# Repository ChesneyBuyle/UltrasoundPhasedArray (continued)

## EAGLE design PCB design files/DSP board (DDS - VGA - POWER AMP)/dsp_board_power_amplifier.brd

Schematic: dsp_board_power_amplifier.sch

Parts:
C1, C19, C28, C37, C55, C64, C73, C91, C100, C109, C127, C136, C154, C172, C190, C208: 1u@6.3V; C0805
C2, C20, C29, C38, C56, C65, C74, C92, C101, C110, C128, C137, C155, C173, C191, C209: 1u6.3V; C0805
C3, C21, C30, C39, C57, C66, C75, C93, C102, C111, C129, C138, C156, C174, C192, C210: 1u; C0603
C4, C11, C12, C22, C31, C40, C47, C48, C58, C67, C76, C84, C85, C94, C103, C112, C121, C122, C130, C139, C157, C175, C193, C211: 10u; C0805
C5, C26, C35, C44, C62, C71, C80, C98, C107, C116, C134, C143, C161, C179, C197, C215: 1u@10V; C0603
C6, C27, C36, C45, C63, C72, C81, C99, C108, C117, C135, C144, C162, C180, C198, C216: 4.7u@25V; C0603
C7, C8, C23, C24, C32, C33, C41, C42, C59, C60, C68, C69, C77, C78, C95, C96, C104, C105, C113, C114, C131, C132, C140, C141, C158, C159, C176, C177, C194, C195, C212, C213: 1u@35V; C0603
C9, C25, C34, C43, C61, C70, C79, C97, C106, C115, C133, C142, C160, C178, C196, C214: 1u@25V; C0603
C10, C13, C14: 100 µF; WCAP-ASLU_6.3X7.7(DXL)
C15, C49, C86, C123: 100n; C0603
C16, C17, C50, C51, C87, C88, C124, C125: 22u; C1206
INPUT: 1935161; PHOENIX_1935161
JP1, JP2, JP5, JP6, JP7, JP8, JP9, JP10, JP13, JP14, JP15, JP16, JP17, JP18, JP21, JP22, JP23, JP24, JP25, JP26, JP29, JP30, JP31, JP32, JP35, JP36, JP39, JP40, JP43, JP44, JP47, JP48: PINHD-1X2; 1X02
L1, L5, L7, L9, L13, L15, L17, L21, L23, L25, L29, L31, L35, L39, L43, L47: BRL3225T4R7M 4.7u; INDC3225X170N
L2, L11, L19, L27: 3.3uH; WE-PD_7345P
L3, L6, L8, L10, L14, L16, L18, L22, L24, L26, L30, L32, L36, L40, L44, L48: FDSD0420-H-100M=P3; IND_FDSD0420-H-100M=P3
LSP1, LSP2, LSP3, LSP4: LSP10
R1, R2, R4, R12, R13, R14, R19, R20, R25, R26, R34, R37, R38, R43, R44, R49, R50, R56, R61, R62, R67, R68, R73, R74, R85, R86, R91, R92, R103, R104, R115, R116, R127, R128, R139, R140: 10k; R0603
R3, R11, R33, R55: 33k; R0603
R5, R6, R15, R16, R21, R22, R27, R28, R39, R40, R45, R46, R51, R52, R63, R64, R69, R70, R75, R76, R87, R88, R93, R94, R105, R106, R117, R118, R129, R130, R141, R142: 10; R0603
R7, R17, R23, R29, R41, R47, R53, R65, R71, R77, R89, R95, R107, R119, R131, R143: 18k; R0603
R8, R18, R24, R30, R42, R48, R54, R66, R72, R78, R90, R96, R108, R120, R132, R144: 1k; R0603
SJ1, SJ2, SJ5, SJ7, SJ9, SJ11, SJ13, SJ15, SJ17, SJ19, SJ21, SJ23, SJ25, SJ27, SJ29, SJ31, SJ35, SJ39, SJ43, SJ47: SJ
SJ3, SJ6, SJ8, SJ10, SJ14, SJ16, SJ18, SJ22, SJ24, SJ26, SJ30, SJ32, SJ36, SJ40, SJ44, SJ48: SJ2W; SJ_2
U1, U6, U8, U10, U14, U16, U18, U22, U24, U26, U30, U32, U36, U40, U44, U48: TLV61046ADBVR; SOT95P280X145-6N
U2, U5, U7, U9, U13, U15, U17, U21, U23, U25, U29, U31, U35, U39, U43, U47: LM48580; BGA12N40P3X4_119X159X62N
U$1, U$10, U$17, U$21: TPS562209; SOT95P280X110-6N
U$2, U$3, U$4, U$5, U$7, U$8, U$9, U$11, U$12, U$13, U$15, U$16, U$18, U$20, U$22, U$24: NSR0520V2T1G; SOD523

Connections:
15V_1: C6.1, R1.2, R7.2, U1.5 (VOUT)
15V_2: C27.1, R13.2, R17.2, U6.5 (VOUT)
15V_3: C45.1, R25.2, R29.2, U10.5 (VOUT)
15V_4: C63.1, R37.2, R41.2, U14.5 (VOUT)
15V_5: C81.1, R49.2, R53.2, U18.5 (VOUT)
15V_6: C99.1, R61.2, R65.2, U22.5 (VOUT)
15V_7: C117.1, R73.2, R77.2, U26.5 (VOUT)
15V_8: C135.1, R85.2, R89.2, U30.5 (VOUT)
15V_9: C36.1, R19.2, R23.2, U8.5 (VOUT)
15V_10: C72.1, R43.2, R47.2, U16.5 (VOUT)
15V_11: C108.1, R67.2, R71.2, U24.5 (VOUT)
15V_12: C144.1, R91.2, R95.2, U32.5 (VOUT)
15V_13: C162.1, R103.2, R107.2, U36.5 (VOUT)
15V_14: C180.1, R115.2, R119.2, U40.5 (VOUT)
15V_15: C198.1, R127.2, R131.2, U44.5 (VOUT)
15V_16: C216.1, R139.2, R143.2, U48.5 (VOUT)
+3V3_A: C3.1, C4.1, C5.1, C16.1, C17.1, C21.1, C22.1, C26.1, C39.1, C40.1, C44.1, C57.1, C58.1, C62.1, L1.1, L2.2, L3.1, L5.1, L6.1, L9.1, L10.1, L13.1, L14.1, R3.2, SJ1.2, SJ3.1, SJ6.1, SJ10.1, SJ14.1, U1.4 (EN), U1.6 (VIN), U2.C2 (~SHDN), U2.C3 (VDD), U5.C2 (~SHDN), U5.C3 (VDD), U6.4 (EN), U6.6 (VIN), U9.C2 (~SHDN), U9.C3 (VDD), U10.4 (EN), U10.6 (VIN), U13.C2 (~SHDN), U13.C3 (VDD), U14.4 (EN), U14.6 (VIN)
+3V3_B: C50.1, C51.1, C75.1, C76.1, C80.1, C93.1, C94.1, C98.1, C111.1, C112.1, C116.1, C129.1, C130.1, C134.1, L11.2, L17.1, L18.1, L21.1, L22.1, L25.1, L26.1, L29.1, L30.1, R11.2, SJ11.2, SJ18.1, SJ22.1, SJ26.1, SJ30.1, U17.C2 (~SHDN), U17.C3 (VDD), U18.4 (EN), U18.6 (VIN), U21.C2 (~SHDN), U21.C3 (VDD), U22.4 (EN), U22.6 (VIN), U25.C2 (~SHDN), U25.C3 (VDD), U26.4 (EN), U26.6 (VIN), U29.C2 (~SHDN), U29.C3 (VDD), U30.4 (EN), U30.6 (VIN)
+3V3_C: C30.1, C31.1, C35.1, C66.1, C67.1, C71.1, C87.1, C88.1, C102.1, C103.1, C107.1, C138.1, C139.1, C143.1, L7.1, L8.1, L15.1, L16.1, L19.2, L23.1, L24.1, L31.1, L32.1, R33.2, SJ8.1, SJ16.1, SJ19.2, SJ24.1, SJ32.1, U7.C2 (~SHDN), U7.C3 (VDD), U8.4 (EN), U8.6 (VIN), U15.C2 (~SHDN), U15.C3 (VDD), U16.4 (EN), U16.6 (VIN), U23.C2 (~SHDN), U23.C3 (VDD), U24.4 (EN), U24.6 (VIN), U31.C2 (~SHDN), U31.C3 (VDD), U32.4 (EN), U32.6 (VIN)
+3V3_D: C124.1, C125.1, C156.1, C157.1, C161.1, C174.1, C175.1, C179.1, C192.1, C193.1, C197.1, C210.1, C211.1, C215.1, L27.2, L35.1, L36.1, L39.1, L40.1, L43.1, L44.1, L47.1, L48.1, R55.2, SJ27.2, SJ36.1, SJ40.1, SJ44.1, SJ48.1, U35.C2 (~SHDN), U35.C3 (VDD), U36.4 (EN), U36.6 (VIN), U39.C2 (~SHDN), U39.C3 (VDD), U40.4 (EN), U40.6 (VIN), U43.C2 (~SHDN), U43.C3 (VDD), U44.4 (EN), U44.6 (VIN), U47.C2 (~SHDN), U47.C3 (VDD), U48.4 (EN), U48.6 (VIN)
GND: C3.2, C4.2, C5.2, C6.2, C9.1, C10.2 (-), C11.2, C12.2, C13.2 (-), C14.2 (-), C16.2, C17.2, C21.2, C22.2, C25.1, C26.2, C27.2, C30.2, C31.2, C34.1, C35.2, C36.2, C39.2, C40.2, C43.1, C44.2, C45.2, C47.2, C48.2, C50.2, C51.2, C57.2, C58.2, C61.1, C62.2, C63.2, C66.2, C67.2, C70.1, C71.2, C72.2, C75.2, C76.2, C79.1, C80.2, C81.2, C84.2, C85.2, C87.2, C88.2, C93.2, C94.2, C97.1, C98.2, C99.2, C102.2, C103.2, C106.1, C107.2, C108.2, C111.2, C112.2, C115.1, C116.2, C117.2, C121.2, C122.2, C124.2, C125.2, C129.2, C130.2, C133.1, C134.2, C135.2, C138.2, C139.2, C142.1, C143.2, C144.2, C156.2, C157.2, C160.1, C161.2, C162.2, C174.2, C175.2, C178.1, C179.2, C180.2, C192.2, C193.2, C196.1, C197.2, C198.2, C210.2, C211.2, C214.1, C215.2, C216.2, INPUT.2, LSP2.MP, LSP4.MP, R2.1, R4.1, R8.1, R12.1, R14.1, R18.1, R20.1, R24.1, R26.1, R30.1, R34.1, R38.1, R42.1, R44.1, R48.1, R50.1, R54.1, R56.1, R62.1, R66.1, R68.1, R72.1, R74.1, R78.1, R86.1, R90.1, R92.1, R96.1, R104.1, R108.1, R116.1, R120.1, R128.1, R132.1, R140.1, R144.1, SJ2.1, SJ3.3, SJ5.1, SJ6.3, SJ7.1, SJ8.3, SJ9.1, SJ10.3, SJ13.1, SJ14.3, SJ15.1, SJ16.3, SJ17.1, SJ18.3, SJ21.1, SJ22.3, SJ23.1, SJ24.3, SJ25.1, SJ26.3, SJ29.1, SJ30.3, SJ31.1, SJ32.3, SJ35.1, SJ36.3, SJ39.1, SJ40.3, SJ43.1, SJ44.3, SJ47.1, SJ48.3, U1.2 (GND), U2.A2 (SGND), U2.D3 (PGND), U5.A2 (SGND), U5.D3 (PGND), U6.2 (GND), U7.A2 (SGND), U7.D3 (PGND), U8.2 (GND), U9.A2 (SGND), U9.D3 (PGND), U10.2 (GND), U13.A2 (SGND), U13.D3 (PGND), U14.2 (GND), U15.A2 (SGND), U15.D3 (PGND), U16.2 (GND), U17.A2 (SGND), U17.D3 (PGND), U18.2 (GND), U21.A2 (SGND), U21.D3 (PGND), U22.2 (GND), U23.A2 (SGND), U23.D3 (PGND), U24.2 (GND), U25.A2 (SGND), U25.D3 (PGND), U26.2 (GND), U29.A2 (SGND), U29.D3 (PGND), U30.2 (GND), U31.A2 (SGND), U31.D3 (PGND), U32.2 (GND), U35.A2 (SGND), U35.D3 (PGND), U36.2 (GND), U39.A2 (SGND), U39.D3 (PGND), U40.2 (GND), U43.A2 (SGND), U43.D3 (PGND), U44.2 (GND), U47.A2 (SGND), U47.D3 (PGND), U48.2 (GND), U$1.1 (GND), U$10.1 (GND), U$17.1 (GND), U$21.1 (GND)
IN+_1: C1.1, JP1.1
IN+_2: C19.1, JP5.1
IN+_3: C37.1, JP9.1
IN+_4: C55.1, JP13.1
IN+_5: C73.1, JP17.1
IN+_6: C91.1, JP21.1
IN+_7: C109.1, JP25.1
IN+_8: C127.1, JP29.1
IN+_9: C28.1, JP7.1
IN+_10: C64.1, JP15.1
IN+_11: C100.1, JP23.1
IN+_12: C136.1, JP31.1
IN+_13: C154.1, JP35.1
IN+_14: C172.1, JP39.1
IN+_15: C190.1, JP43.1
IN+_16: C208.1, JP47.1
IN-_1: C2.1, SJ2.2
IN-_2: C20.1, SJ5.2
IN-_3: C38.1, SJ9.2
IN-_4: C56.1, SJ13.2
IN-_5: C74.1, SJ17.2
IN-_6: C92.1, SJ21.2
IN-_7: C110.1, SJ25.2
IN-_8: C128.1, SJ29.2
IN-_9: C29.1, SJ7.2
IN-_10: C65.1, SJ15.2
IN-_11: C101.1, SJ23.2
IN-_12: C137.1, SJ31.2
IN-_13: C155.1, SJ35.2
IN-_14: C173.1, SJ39.2
IN-_15: C191.1, SJ43.2
IN-_16: C209.1, SJ47.2
unnamed: C1.2, U2.A3 (IN+)
unnamed: C2.2, U2.B3 (IN-)
unnamed: SJ3.2, U2.B2 (GAIN)
unnamed: C7.1, U2.A1 (OUT+)
unnamed: C8.1, U2.B1 (OUT-)
unnamed: C7.2, R1.1, R5.1
unnamed: L1.2, U2.D2 (SW), U$2.2 (A)
unnamed: C9.2, U2.C1 (VAMP), U2.D1 (VBST), U$2.1 (C)
unnamed: C8.2, R2.2, R6.1
unnamed: R3.1, R4.2, U$1.4 (VFB)
unnamed: L3.2, U1.1 (SW)
unnamed: R7.1, R8.2, U1.3 (FB)
unnamed: C15.1, U$1.6 (VBST)
unnamed: C15.2, L2.1, U$1.2 (SW)
unnamed: R11.1, R12.2, U$10.4 (VFB)
unnamed: C49.1, U$10.6 (VBST)
unnamed: C49.2, L11.1, U$10.2 (SW)
unnamed: C19.2, U5.A3 (IN+)
unnamed: C20.2, U5.B3 (IN-)
unnamed: SJ6.2, U5.B2 (GAIN)
unnamed: C23.1, U5.A1 (OUT+)
unnamed: C24.1, U5.B1 (OUT-)
unnamed: C23.2, R13.1, R15.1
unnamed: C24.2, R14.2, R16.1
unnamed: L6.2, U6.1 (SW)
unnamed: R17.1, R18.2, U6.3 (FB)
unnamed: L5.2, U5.D2 (SW), U$3.2 (A)
unnamed: C25.2, U5.C1 (VAMP), U5.D1 (VBST), U$3.1 (C)
unnamed: C28.2, U7.A3 (IN+)
unnamed: C29.2, U7.B3 (IN-)
unnamed: SJ8.2, U7.B2 (GAIN)
unnamed: C32.1, U7.A1 (OUT+)
unnamed: C33.1, U7.B1 (OUT-)
unnamed: C32.2, R19.1, R21.1
unnamed: C33.2, R20.2, R22.1
unnamed: L8.2, U8.1 (SW)
unnamed: R23.1, R24.2, U8.3 (FB)
unnamed: L7.2, U7.D2 (SW), U$4.2 (A)
unnamed: C34.2, U7.C1 (VAMP), U7.D1 (VBST), U$4.1 (C)
unnamed: C37.2, U9.A3 (IN+)
unnamed: C38.2, U9.B3 (IN-)
unnamed: SJ10.2, U9.B2 (GAIN)
unnamed: C41.1, U9.A1 (OUT+)
unnamed: C42.1, U9.B1 (OUT-)
unnamed: C41.2, R25.1, R27.1
unnamed: C42.2, R26.2, R28.1
unnamed: L10.2, U10.1 (SW)
unnamed: R29.1, R30.2, U10.3 (FB)
unnamed: L9.2, U9.D2 (SW), U$5.2 (A)
unnamed: C43.2, U9.C1 (VAMP), U9.D1 (VBST), U$5.1 (C)
unnamed: R33.1, R34.2, U$17.4 (VFB)
unnamed: C86.1, U$17.6 (VBST)
unnamed: C86.2, L19.1, U$17.2 (SW)
unnamed: R55.1, R56.2, U$21.4 (VFB)
unnamed: C123.1, U$21.6 (VBST)
unnamed: C123.2, L27.1, U$21.2 (SW)
unnamed: C55.2, U13.A3 (IN+)
unnamed: C56.2, U13.B3 (IN-)
unnamed: SJ14.2, U13.B2 (GAIN)
unnamed: C59.1, U13.A1 (OUT+)
unnamed: C60.1, U13.B1 (OUT-)
unnamed: C59.2, R37.1, R39.1
unnamed: C60.2, R38.2, R40.1
unnamed: L14.2, U14.1 (SW)
unnamed: R41.1, R42.2, U14.3 (FB)
unnamed: L13.2, U13.D2 (SW), U$7.2 (A)
unnamed: C61.2, U13.C1 (VAMP), U13.D1 (VBST), U$7.1 (C)
unnamed: C64.2, U15.A3 (IN+)
unnamed: C65.2, U15.B3 (IN-)
unnamed: SJ16.2, U15.B2 (GAIN)
unnamed: C68.1, U15.A1 (OUT+)
unnamed: C69.1, U15.B1 (OUT-)
unnamed: C68.2, R43.1, R45.1
unnamed: C69.2, R44.2, R46.1
unnamed: L16.2, U16.1 (SW)
unnamed: R47.1, R48.2, U16.3 (FB)
unnamed: L15.2, U15.D2 (SW), U$8.2 (A)
unnamed: C70.2, U15.C1 (VAMP), U15.D1 (VBST), U$8.1 (C)
unnamed: C73.2, U17.A3 (IN+)
unnamed: C74.2, U17.B3 (IN-)
unnamed: SJ18.2, U17.B2 (GAIN)
unnamed: C77.1, U17.A1 (OUT+)
unnamed: C78.1, U17.B1 (OUT-)
unnamed: C77.2, R49.1, R51.1
unnamed: C78.2, R50.2, R52.1
unnamed: L18.2, U18.1 (SW)
unnamed: R53.1, R54.2, U18.3 (FB)
unnamed: L17.2, U17.D2 (SW), U$9.2 (A)
unnamed: C79.2, U17.C1 (VAMP), U17.D1 (VBST), U$9.1 (C)
unnamed: C91.2, U21.A3 (IN+)
unnamed: C92.2, U21.B3 (IN-)
unnamed: SJ22.2, U21.B2 (GAIN)
unnamed: C95.1, U21.A1 (OUT+)
unnamed: C96.1, U21.B1 (OUT-)
unnamed: C95.2, R61.1, R63.1
unnamed: C96.2, R62.2, R64.1
unnamed: L22.2, U22.1 (SW)
unnamed: R65.1, R66.2, U22.3 (FB)
unnamed: L21.2, U21.D2 (SW), U$11.2 (A)
unnamed: C97.2, U21.C1 (VAMP), U21.D1 (VBST), U$11.1 (C)
unnamed: C100.2, U23.A3 (IN+)
unnamed: C101.2, U23.B3 (IN-)
unnamed: SJ24.2, U23.B2 (GAIN)
unnamed: C104.1, U23.A1 (OUT+)
unnamed: C105.1, U23.B1 (OUT-)
unnamed: C104.2, R67.1, R69.1
unnamed: C105.2, R68.2, R70.1
unnamed: L24.2, U24.1 (SW)
unnamed: R71.1, R72.2, U24.3 (FB)
unnamed: L23.2, U23.D2 (SW), U$12.2 (A)
unnamed: C106.2, U23.C1 (VAMP), U23.D1 (VBST), U$12.1 (C)
unnamed: C109.2, U25.A3 (IN+)
unnamed: C110.2, U25.B3 (IN-)
unnamed: SJ26.2, U25.B2 (GAIN)
unnamed: C113.1, U25.A1 (OUT+)
unnamed: C114.1, U25.B1 (OUT-)
unnamed: C113.2, R73.1, R75.1
unnamed: C114.2, R74.2, R76.1
unnamed: L26.2, U26.1 (SW)
unnamed: R77.1, R78.2, U26.3 (FB)
unnamed: L25.2, U25.D2 (SW), U$13.2 (A)
unnamed: C115.2, U25.C1 (VAMP), U25.D1 (VBST), U$13.1 (C)
unnamed: C127.2, U29.A3 (IN+)
unnamed: C128.2, U29.B3 (IN-)
unnamed: SJ30.2, U29.B2 (GAIN)
unnamed: C131.1, U29.A1 (OUT+)
unnamed: C132.1, U29.B1 (OUT-)
unnamed: C131.2, R85.1, R87.1
unnamed: C132.2, R86.2, R88.1
unnamed: L30.2, U30.1 (SW)
unnamed: R89.1, R90.2, U30.3 (FB)
unnamed: L29.2, U29.D2 (SW), U$15.2 (A)
unnamed: C133.2, U29.C1 (VAMP), U29.D1 (VBST), U$15.1 (C)
unnamed: C136.2, U31.A3 (IN+)
unnamed: C137.2, U31.B3 (IN-)
unnamed: SJ32.2, U31.B2 (GAIN)
unnamed: C140.1, U31.A1 (OUT+)
unnamed: C141.1, U31.B1 (OUT-)
unnamed: C140.2, R91.1, R93.1
unnamed: C141.2, R92.2, R94.1
unnamed: L32.2, U32.1 (SW)
unnamed: R95.1, R96.2, U32.3 (FB)
unnamed: L31.2, U31.D2 (SW), U$16.2 (A)
unnamed: C142.2, U31.C1 (VAMP), U31.D1 (VBST), U$16.1 (C)
unnamed: C154.2, U35.A3 (IN+)
unnamed: C155.2, U35.B3 (IN-)
unnamed: SJ36.2, U35.B2 (GAIN)
unnamed: C158.1, U35.A1 (OUT+)
unnamed: C159.1, U35.B1 (OUT-)
unnamed: C158.2, R103.1, R105.1
unnamed: C159.2, R104.2, R106.1
unnamed: L36.2, U36.1 (SW)
unnamed: R107.1, R108.2, U36.3 (FB)
unnamed: L35.2, U35.D2 (SW), U$18.2 (A)
unnamed: C160.2, U35.C1 (VAMP), U35.D1 (VBST), U$18.1 (C)
unnamed: C172.2, U39.A3 (IN+)
unnamed: C173.2, U39.B3 (IN-)
unnamed: SJ40.2, U39.B2 (GAIN)
unnamed: C176.1, U39.A1 (OUT+)
unnamed: C177.1, U39.B1 (OUT-)
unnamed: C176.2, R115.1, R117.1
unnamed: C177.2, R116.2, R118.1
unnamed: L40.2, U40.1 (SW)
unnamed: R119.1, R120.2, U40.3 (FB)
unnamed: L39.2, U39.D2 (SW), U$20.2 (A)
unnamed: C178.2, U39.C1 (VAMP), U39.D1 (VBST), U$20.1 (C)
unnamed: C190.2, U43.A3 (IN+)
unnamed: C191.2, U43.B3 (IN-)
unnamed: SJ44.2, U43.B2 (GAIN)
unnamed: C194.1, U43.A1 (OUT+)
unnamed: C195.1, U43.B1 (OUT-)
unnamed: C194.2, R127.1, R129.1
unnamed: C195.2, R128.2, R130.1
unnamed: L44.2, U44.1 (SW)
unnamed: R131.1, R132.2, U44.3 (FB)
unnamed: L43.2, U43.D2 (SW), U$22.2 (A)
unnamed: C196.2, U43.C1 (VAMP), U43.D1 (VBST), U$22.1 (C)
unnamed: C208.2, U47.A3 (IN+)
unnamed: C209.2, U47.B3 (IN-)
unnamed: SJ48.2, U47.B2 (GAIN)
unnamed: C212.1, U47.A1 (OUT+)
unnamed: C213.1, U47.B1 (OUT-)
unnamed: C212.2, R139.1, R141.1
unnamed: C213.2, R140.2, R142.1
unnamed: L48.2, U48.1 (SW)
unnamed: R143.1, R144.2, U48.3 (FB)
unnamed: L47.2, U47.D2 (SW), U$24.2 (A)
unnamed: C214.2, U47.C1 (VAMP), U47.D1 (VBST), U$24.1 (C)
OUT+_1: JP2.1, R5.2
OUT+_2: JP6.1, R15.2
OUT+_3: JP10.1, R27.2
OUT+_4: JP14.1, R39.2
OUT+_5: JP18.1, R51.2
OUT+_6: JP22.1, R63.2
OUT+_7: JP26.1, R75.2
OUT+_8: JP30.1, R87.2
OUT+_9: JP8.1, R21.2
OUT+_10: JP16.1, R45.2
OUT+_11: JP24.1, R69.2
OUT+_12: JP32.1, R93.2
OUT+_13: JP36.1, R105.2
OUT+_14: JP40.1, R117.2
OUT+_15: JP44.1, R129.2
OUT+_16: JP48.1, R141.2
OUT-_1: JP2.2, R6.2
OUT-_2: JP6.2, R16.2
OUT-_3: JP10.2, R28.2
OUT-_4: JP14.2, R40.2
OUT-_5: JP18.2, R52.2
OUT-_6: JP22.2, R64.2
OUT-_7: JP26.2, R76.2
OUT-_8: JP30.2, R88.2
OUT-_9: JP8.2, R22.2
OUT-_10: JP16.2, R46.2
OUT-_11: JP24.2, R70.2
OUT-_12: JP32.2, R94.2
OUT-_13: JP36.2, R106.2
OUT-_14: JP40.2, R118.2
OUT-_15: JP44.2, R130.2
OUT-_16: JP48.2, R142.2
VIN: C10.1 (+), C11.1, C12.1, C13.1 (+), C14.1 (+), C47.1, C48.1, C84.1, C85.1, C121.1, C122.1, INPUT.1, LSP1.MP, LSP3.MP, SJ1.1, SJ11.1, SJ19.1, SJ27.1, U$1.3 (VIN), U$1.5 (EN), U$10.3 (VIN), U$10.5 (EN), U$17.3 (VIN), U$17.5 (EN), U$21.3 (VIN), U$21.5 (EN)

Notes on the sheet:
Buck converters (3.3V)
Input voltage can be directly connected to 3.3V voltages lines through voltage jumpers
Power amplifier (PA) stages
Input voltage and decoupling
Power amplifier (part of DSP board)

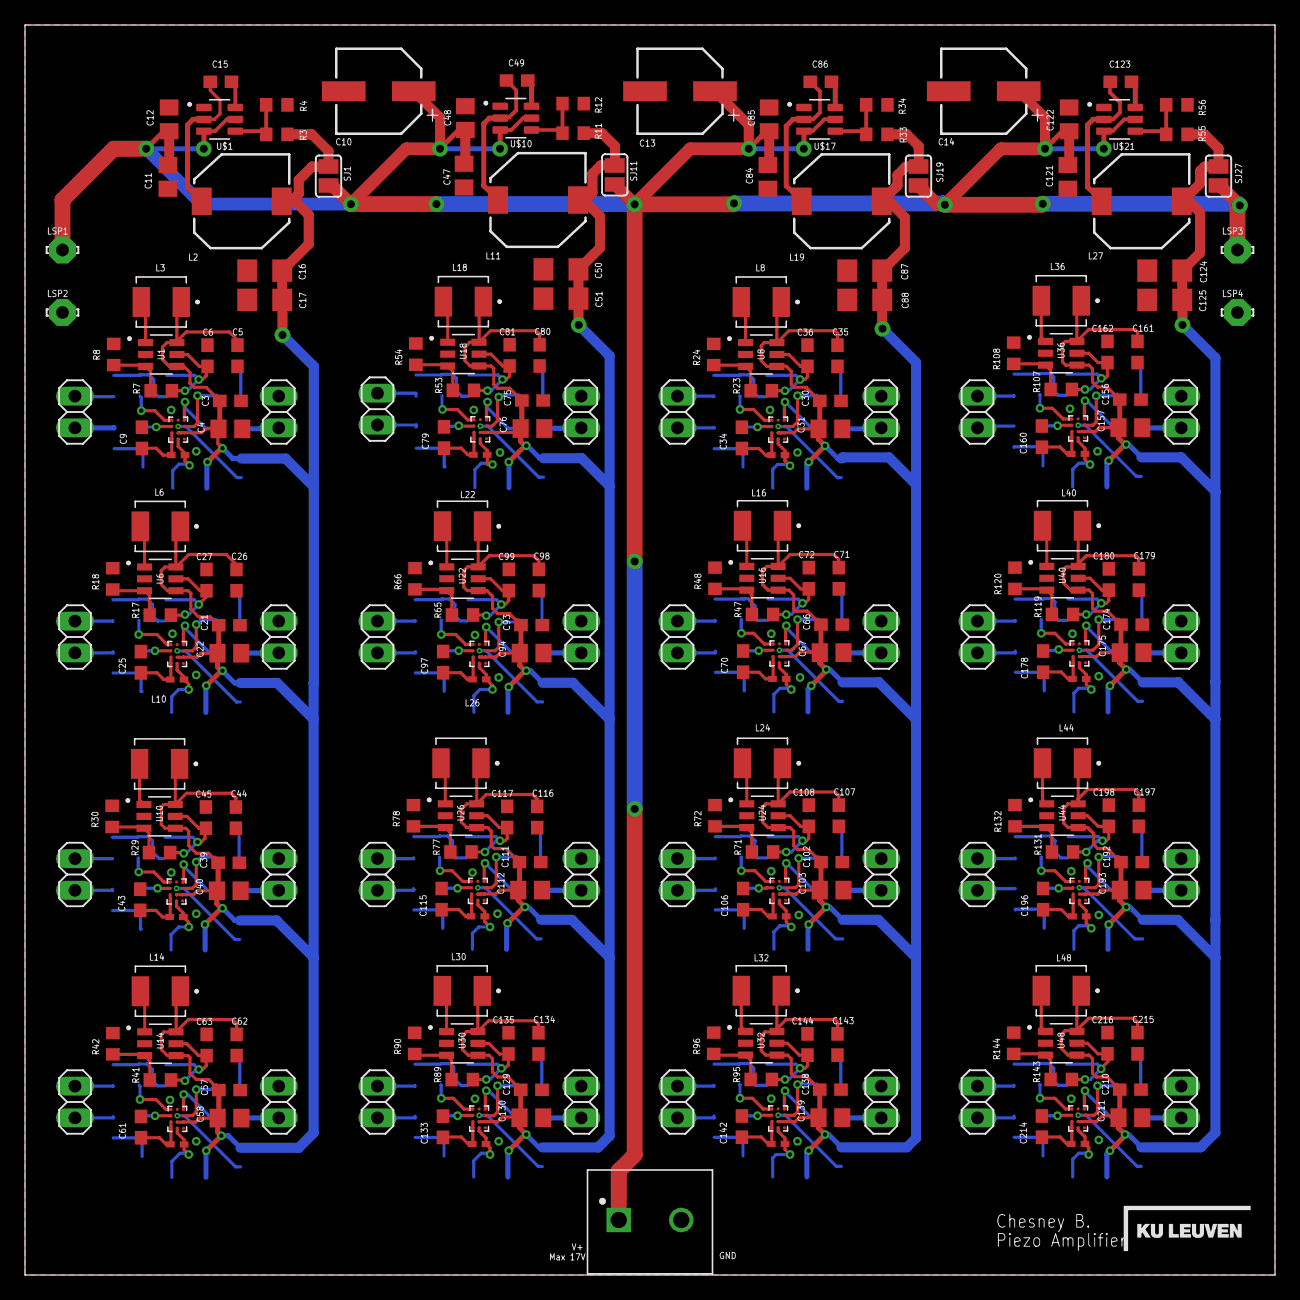
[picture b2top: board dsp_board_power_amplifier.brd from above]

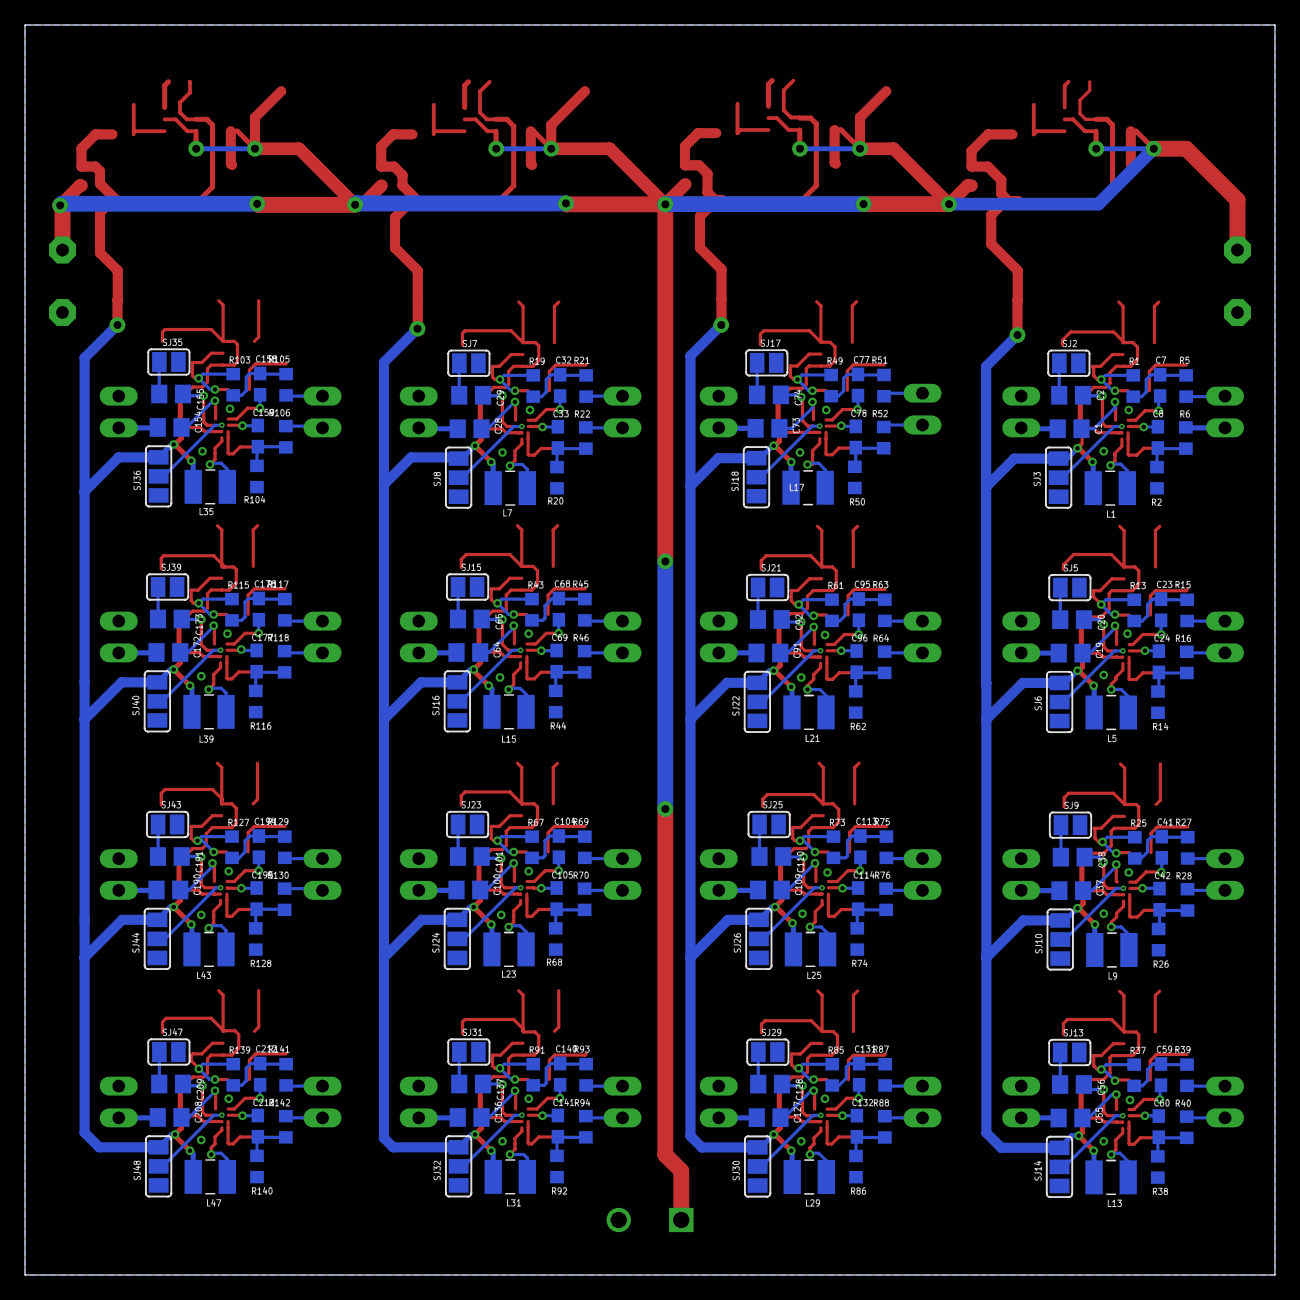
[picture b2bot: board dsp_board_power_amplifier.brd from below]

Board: 2 copper layers, 100.0 x 100.0 mm, 432 parts (176 on the bottom side), 274 nets.
